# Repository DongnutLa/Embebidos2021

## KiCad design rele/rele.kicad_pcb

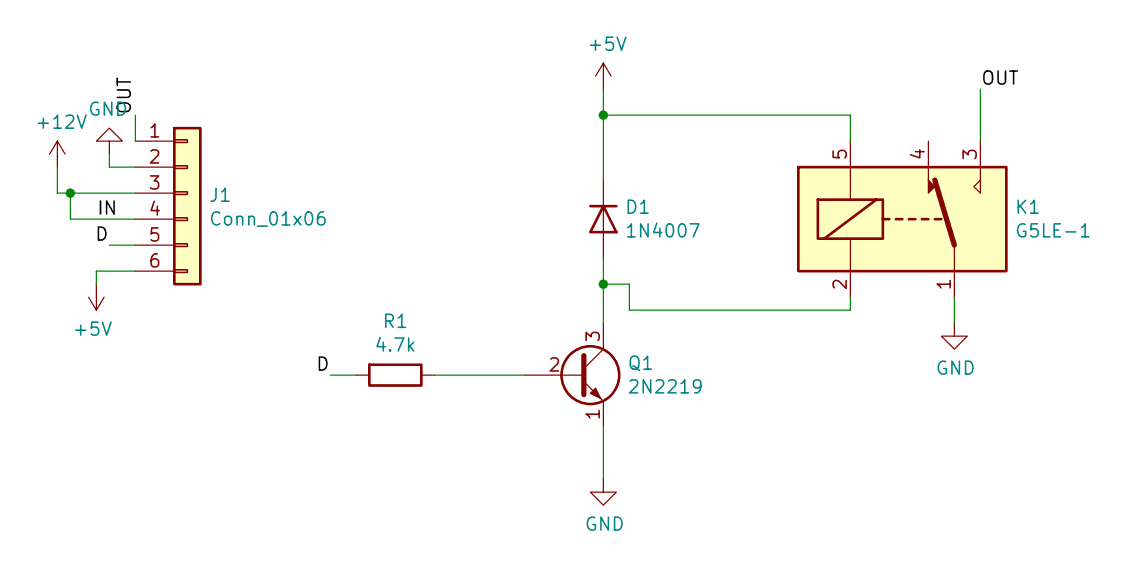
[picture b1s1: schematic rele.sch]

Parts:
D1: 1N4007; D_DO-41_SOD81_P10.16mm_Horizontal
J1: Conn_01x06; PinSocket_1x06_P2.54mm_Horizontal
K1: G5LE-1; Relay_SPDT_Omron-G5LE-1
Q1: 2N2219; TO-92_HandSolder
R1: 4.7k; R_Axial_DIN0207_L6.3mm_D2.5mm_P15.24mm_Horizontal

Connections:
+5V: D1.1 (K), J1.6, K1.5
+12V: J1.3, J1.4
/D: J1.5, R1.2
/OUT: J1.1, K1.3
GND: J1.2, K1.1, Q1.1 (E)
unnamed: D1.2 (A), K1.2, Q1.3 (C)
unnamed: Q1.2 (B), R1.1

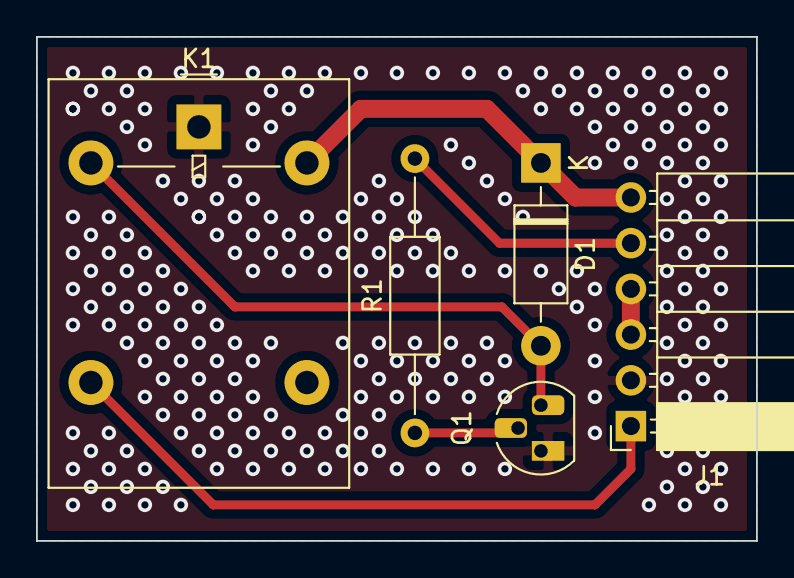
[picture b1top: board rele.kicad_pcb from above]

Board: 2 copper layers, 40.0 x 28.0 mm, 5 parts (0 on the bottom side), 7 nets.

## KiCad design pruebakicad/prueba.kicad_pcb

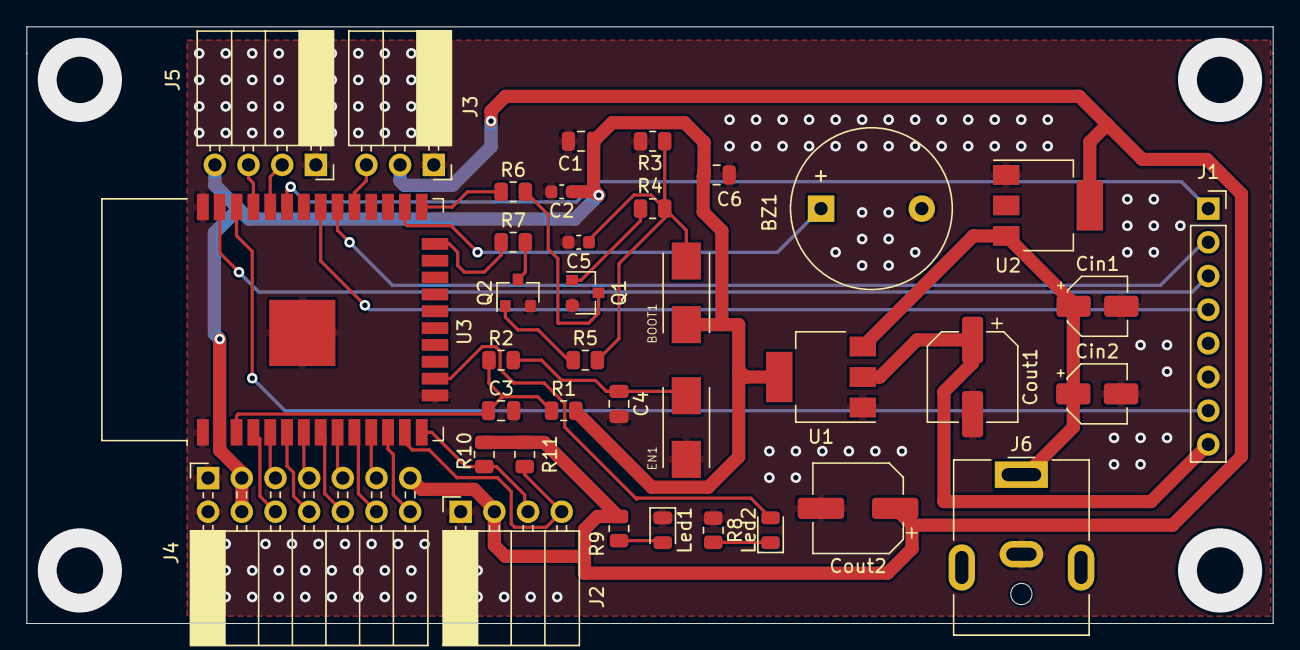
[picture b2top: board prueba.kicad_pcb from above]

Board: 2 copper layers, 94.0 x 45.0 mm, 37 parts (0 on the bottom side), 36 nets.

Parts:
BOOT1: 147873-1; SW_147873-1
BZ1: Buzzer; Buzzer_12x9.5RM7.6
C1, C4, C6: 0.1uF; C_0805_2012Metric
C2: 10uF; C_0603_1608Metric
C3: 1uF; C_0805_2012Metric
C5: 1nF; C_0603_1608Metric
Cin1, Cin2: 10u; CP_Elec_4x5.7
Cout1, Cout2: 100u; CP_Elec_6.3x5.9
EN1: 147873-1; SW_147873-1
J1: Conn_01x08_RC522; PinSocket_1x08_P2.54mm_Vertical
J2: Conn_01x04_MountingPin; PinSocket_1x04_P2.54mm_Horizontal
J3: Conn_01x03; PinSocket_1x03_P2.54mm_Horizontal
J4: Conn_2Rows-15Pins; PinSocket_2x07_P2.54mm_Horizontal
J5: Conn_01x04; PinSocket_1x04_P2.54mm_Horizontal
J6: Conn_01x02; BarrelJack_CUI_PJ-063AH_Horizontal
Led1: LED_RED; LED_0805_2012Metric
Led2: LED_BLUE; LED_0805_2012Metric
Q1, Q2: BSS138; SOT-23
R1, R3, R10, R11: 10k; R_0805_2012Metric
R2, R6, R7: 0R; R_0805_2012Metric
R4, R5: 1k; R_0805_2012Metric
R8, R9: 220; R_0805_2012Metric
U1: TLV1117-33; SOT-223
U2: TLV1117-50; SOT-223
U3: ESP32-WROOM-32

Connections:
+3V3: BOOT1.1, C1.1, C2.1, C6.2, Cout1.1, J1.8, J4.3, J4.4, J5.4, R1.2, U1.2, U1.4, U3.2
+5V: Cout2.1, J2.2, J3.2, J4.13, R9.2, R10.1, R11.2, U2.4
+12V: Cin1.1, Cin2.1, J6.1, U1.3, U2.3
/BUZ: BZ1.1, U3.26
/IO13: Led2.2, U3.16
/IO25: J4.12, U3.10
/IO26: J4.11, U3.11
/IO27: J4.14, U3.12
/IO32: J4.10, U3.8
/IO33: J4.9, U3.9
/IO34: J4.8, U3.6
/IO35: J4.7, U3.7
/MISO: J1.4, U3.31
/MOSI: J1.3, U3.37
/OBS: J3.3, U3.29
/RST: J1.7, U3.36
/RXD0: J5.2, U3.34
/SCK: J1.2, U3.30
/SCLi2c: J2.4, R11.1, U3.13
/SDAi2c: J2.3, R10.2, U3.14
/SDAspi: J1.1, U3.33
/TXD0: J5.3, U3.35
/esp32-wroom/EN: C3.1, R1.1, R2.1, U3.3
/esp32-wroom/IO0: R6.1, U3.25
/esp32-wroom/IO2: R7.1, U3.24
/sensVN: J4.5, U3.5
/sensVP: J4.6, U3.4
GND: BZ1.2, C1.2, C2.2, C3.2, C4.2, C5.2, C6.1, Cin1.2, Cin2.2, Cout1.2, Cout2.2, EN1.1, J1.6, J2.1, J3.1, J4.1, J4.2, J5.1, J6.2, Led1.1, Q1.2, Q2.2, R3.2, R8.1, U1.1, U2.1, U3.1, U3.15, U3.38, U3.39
unnamed: BOOT1.2, C5.1, R3.1, R4.2, R5.2
unnamed: C4.1, EN1.2, R2.2
unnamed: Led1.2, R9.1
unnamed: Led2.1, R8.2
unnamed: Q1.1, R4.1
unnamed: Q1.3, R6.2
unnamed: Q2.1, R5.1
unnamed: Q2.3, R7.2

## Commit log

2021-04-15 esp32-wroom
2021-04-15 pins
2021-04-20 More peripherals
    Added some peripherals and last ones were fixed
2021-04-22 Added_gpios
2021-04-22 uart_added
2021-04-27 footprints
    Footprints added
2021-04-29 footprints
    Finished footprints
2021-04-29 pcb1.0
    created pcb
2021-07-01 wires updated
2021-07-01 wires
2021-07-06 pistas
2021-07-06 ruteo completo
2021-07-06 asss
2021-07-06 Hola
2021-07-06 asdsad
2021-07-06 tierras
2021-07-07 full
2021-07-07 holes
2021-07-07 Update prueba.kicad_pcb-bak
2021-07-08 huecos gnd
2021-07-08 gerber
2021-07-08 nomap
